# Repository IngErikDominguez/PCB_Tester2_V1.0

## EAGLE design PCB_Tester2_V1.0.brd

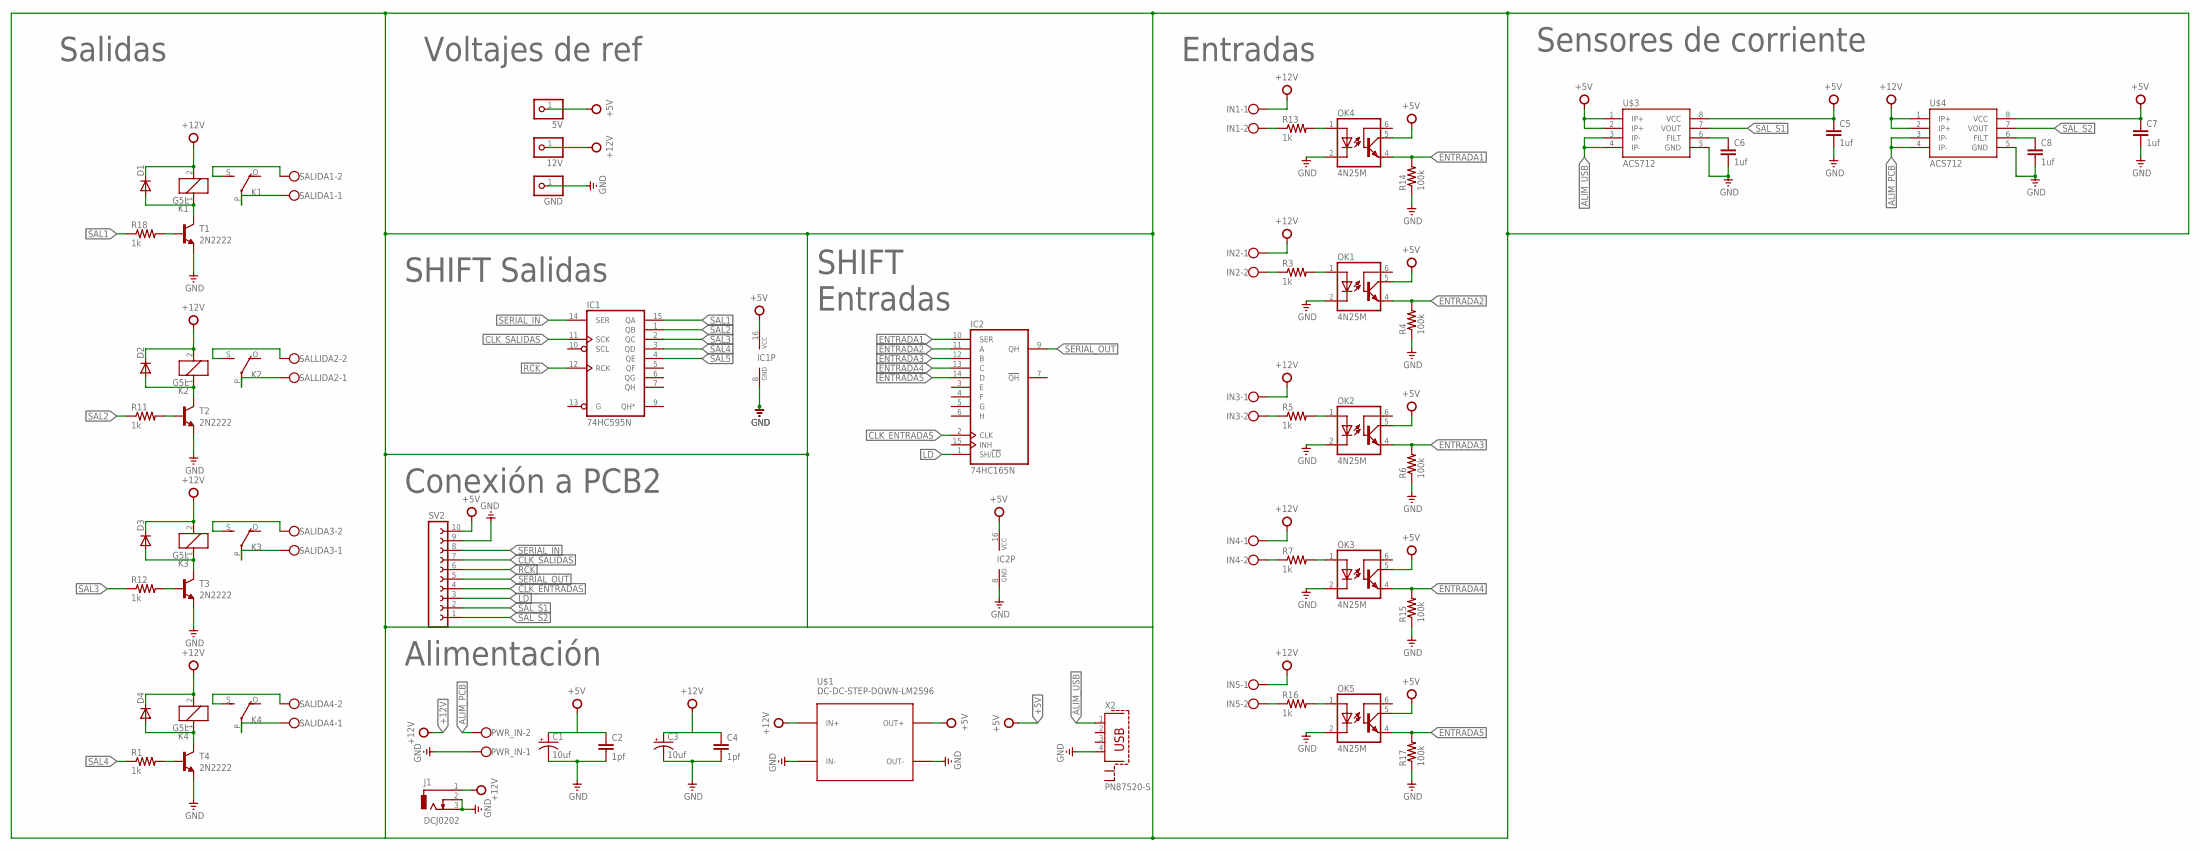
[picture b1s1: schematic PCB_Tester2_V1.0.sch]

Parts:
5V, 12V: PINHD-1X1; 1X01
C1, C3: 10uf; E2,5-6
C2, C4: 1pf; C2.5-3
C5, C6, C7, C8: 1uf; C2.5-3
D1, D2, D3, D4: 1N4148DO35-7; DO35-7
GND: PINHD-1X1; 1X01
IC1: 74HC595N; DIL16
IC2: 74HC165N; DIL16
IN1, IN2, IN3, IN4, IN5: W237-102
J1: DCJ0202
K1, K2, K3, K4: G5L; G5LE
OK1, OK2, OK3, OK4, OK5: 4N25M; DIL06
PWR_IN: W237-102
R1, R3, R5, R7, R11, R12, R13, R16, R18: 1k; 0207/7
R4, R6, R14, R15, R17: 100k; 0207/7
SALIDA1, SALIDA3, SALIDA4: W237-102
SALLIDA2: W237-102
SV2: FE10-1; FE10
T1, T2, T3, T4: 2N2222; TO18
U$1: DC-DC-STEP-DOWN-LM2596
U$3, U$4: ACS712; SO08
X2: PN87520-S

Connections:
+5V: 5V.1, C1.+, C2.1, C5.1, C7.1, IC1.16 (VCC), IC2.16 (VCC), OK1.5 (COL), OK2.5 (COL), OK3.5 (COL), OK4.5 (COL), OK5.5 (COL), SV2.10, U$1.OUT+, U$3.1 (IP+), U$3.2 (IP+), U$3.8 (VCC), U$4.8 (VCC)
+12V: 12V.1, C3.+, C4.1, D1.C, D2.C, D3.C, D4.C, IN1.1, IN2.1, IN3.1, IN4.1, IN5.1, J1.1, K1.2, K2.2, K3.2, K4.2, U$1.IN+, U$4.1 (IP+), U$4.2 (IP+)
ALIM_PCB: PWR_IN.2, U$4.3 (IP-), U$4.4 (IP-)
ALIM_USB: U$3.3 (IP-), U$3.4 (IP-), X2.1
CLK_ENTRADAS: IC2.2 (CLK), SV2.4
CLK_SALIDAS: IC1.11 (SCK), SV2.7
ENTRADA1: IC2.10 (SER), OK4.4 (EMI), R14.2
ENTRADA2: IC2.11 (A), OK1.4 (EMI), R4.2
ENTRADA3: IC2.12 (B), OK2.4 (EMI), R6.2
ENTRADA4: IC2.13 (C), OK3.4 (EMI), R15.2
ENTRADA5: IC2.14 (D), OK5.4 (EMI), R17.2
GND: C1.-, C2.2, C3.-, C4.2, C5.2, C6.2, C7.2, C8.2, GND.1, IC1.8 (GND), IC2.8 (GND), J1.2, J1.3, OK1.2 (C), OK2.2 (C), OK3.2 (C), OK4.2 (C), OK5.2 (C), PWR_IN.1, R4.1, R6.1, R14.1, R15.1, R17.1, SV2.9, T1.1 (E), T2.1 (E), T3.1 (E), T4.1 (E), U$1.IN-, U$1.OUT-, U$3.5 (GND), U$4.5 (GND), X2.4
LD: IC2.1 (SH/!LD), SV2.3
unnamed: D4.A, K4.1, T4.3 (C)
unnamed: R1.2, T4.2 (B)
unnamed: K4.S, SALIDA4.2
unnamed: K4.P, SALIDA4.1
unnamed: IN2.2, R3.1
unnamed: OK1.1 (A), R3.2
unnamed: IN3.2, R5.1
unnamed: OK2.1 (A), R5.2
unnamed: D2.A, K2.1, T2.3 (C)
unnamed: R11.2, T2.2 (B)
unnamed: K2.S, SALLIDA2.2
unnamed: K2.P, SALLIDA2.1
unnamed: D3.A, K3.1, T3.3 (C)
unnamed: R12.2, T3.2 (B)
unnamed: K3.S, SALIDA3.2
unnamed: K3.P, SALIDA3.1
unnamed: IN1.2, R13.1
unnamed: OK4.1 (A), R13.2
unnamed: IN4.2, R7.1
unnamed: OK3.1 (A), R7.2
unnamed: IN5.2, R16.1
unnamed: OK5.1 (A), R16.2
unnamed: D1.A, K1.1, T1.3 (C)
unnamed: R18.2, T1.2 (B)
unnamed: K1.S, SALIDA1.2
unnamed: K1.P, SALIDA1.1
unnamed: C6.1, U$3.6 (FILT)
unnamed: C8.1, U$4.6 (FILT)
RCK: IC1.12 (RCK), SV2.6
SAL1: IC1.15 (QA), R18.1
SAL2: IC1.1 (QB), R11.1
SAL3: IC1.2 (QC), R12.1
SAL4: IC1.3 (QD), R1.1
SAL5: IC1.4 (QE)
SAL_S1: SV2.2, U$3.7 (VOUT)
SAL_S2: SV2.1, U$4.7 (VOUT)
SERIAL_IN: IC1.14 (SER), SV2.8
SERIAL_OUT: IC2.9 (QH), SV2.5

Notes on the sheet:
Alimentación
Voltajes de ref
Salidas
Entradas
SHIFT Salidas
SHIFT Entradas
Conexión a PCB2
Sensores de corriente

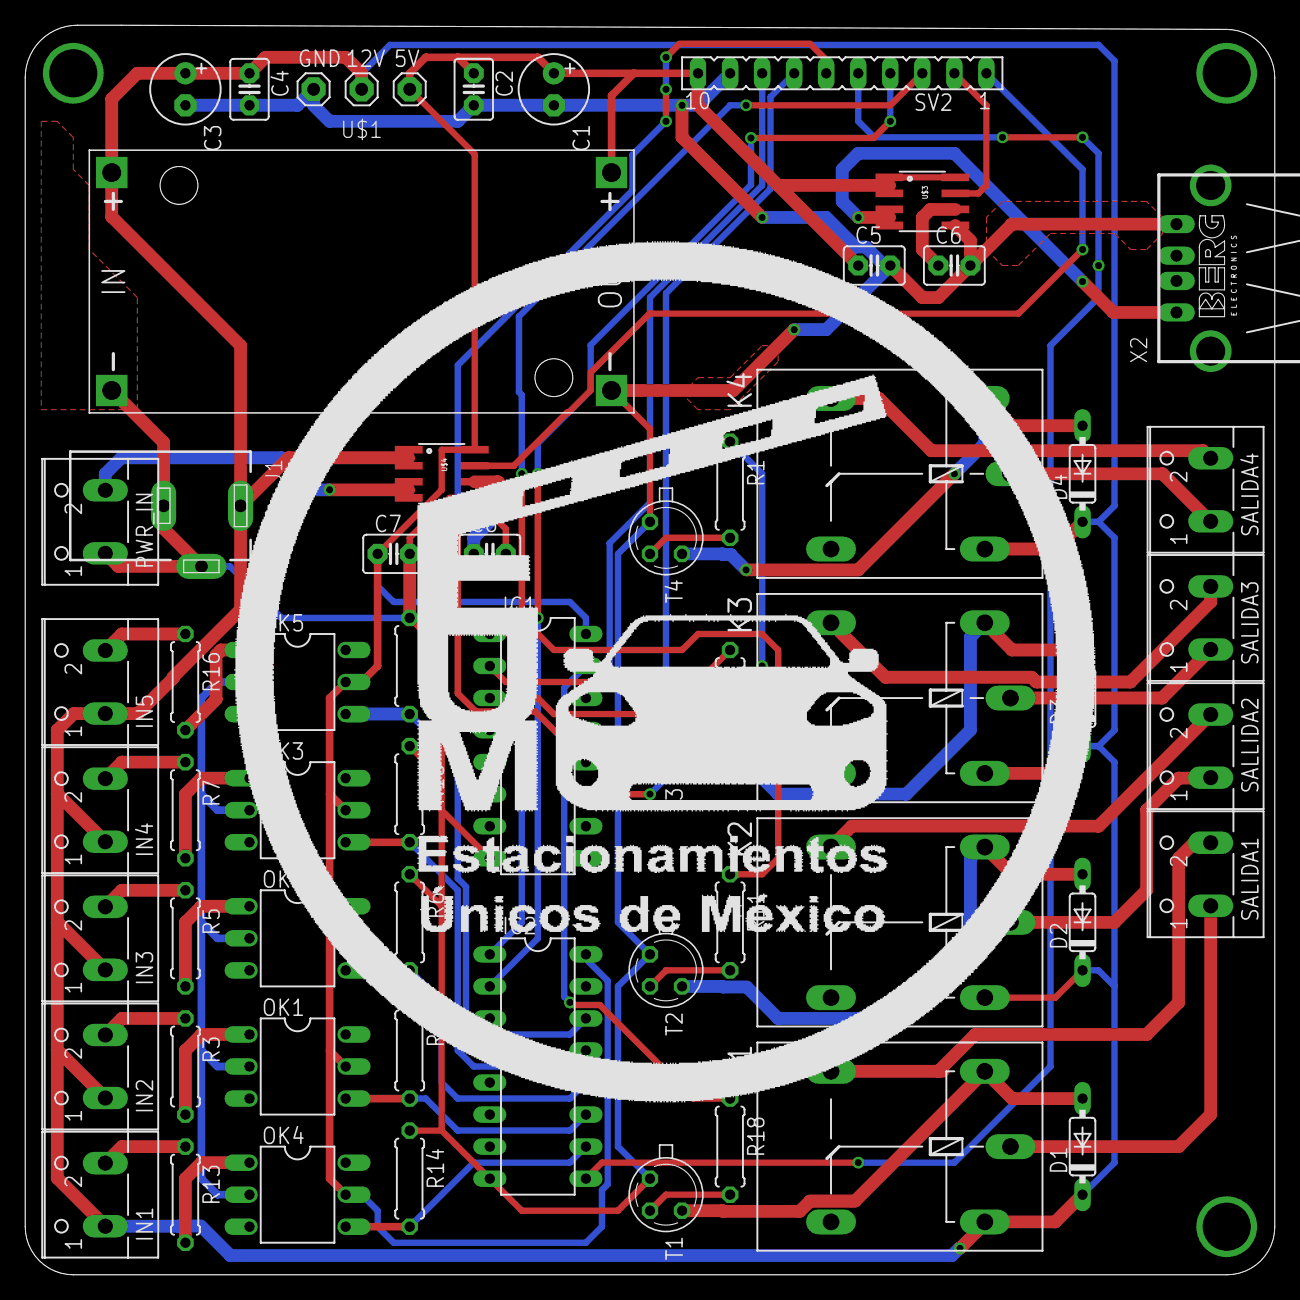
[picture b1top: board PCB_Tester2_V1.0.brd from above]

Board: 2 copper layers, 99.1 x 99.1 mm, 60 parts (0 on the bottom side), 50 nets.

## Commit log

2019-03-07 V1.0
    PRimer esquematico y ruteado del segundo PCB Tester
2019-03-08 V1.0
    Máscara agregada

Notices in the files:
parts and their libraries:
diy-modules: Released under the Creative Commons Attribution 4.0 International License: http://creativecommons.org/licenses/by/4.0
